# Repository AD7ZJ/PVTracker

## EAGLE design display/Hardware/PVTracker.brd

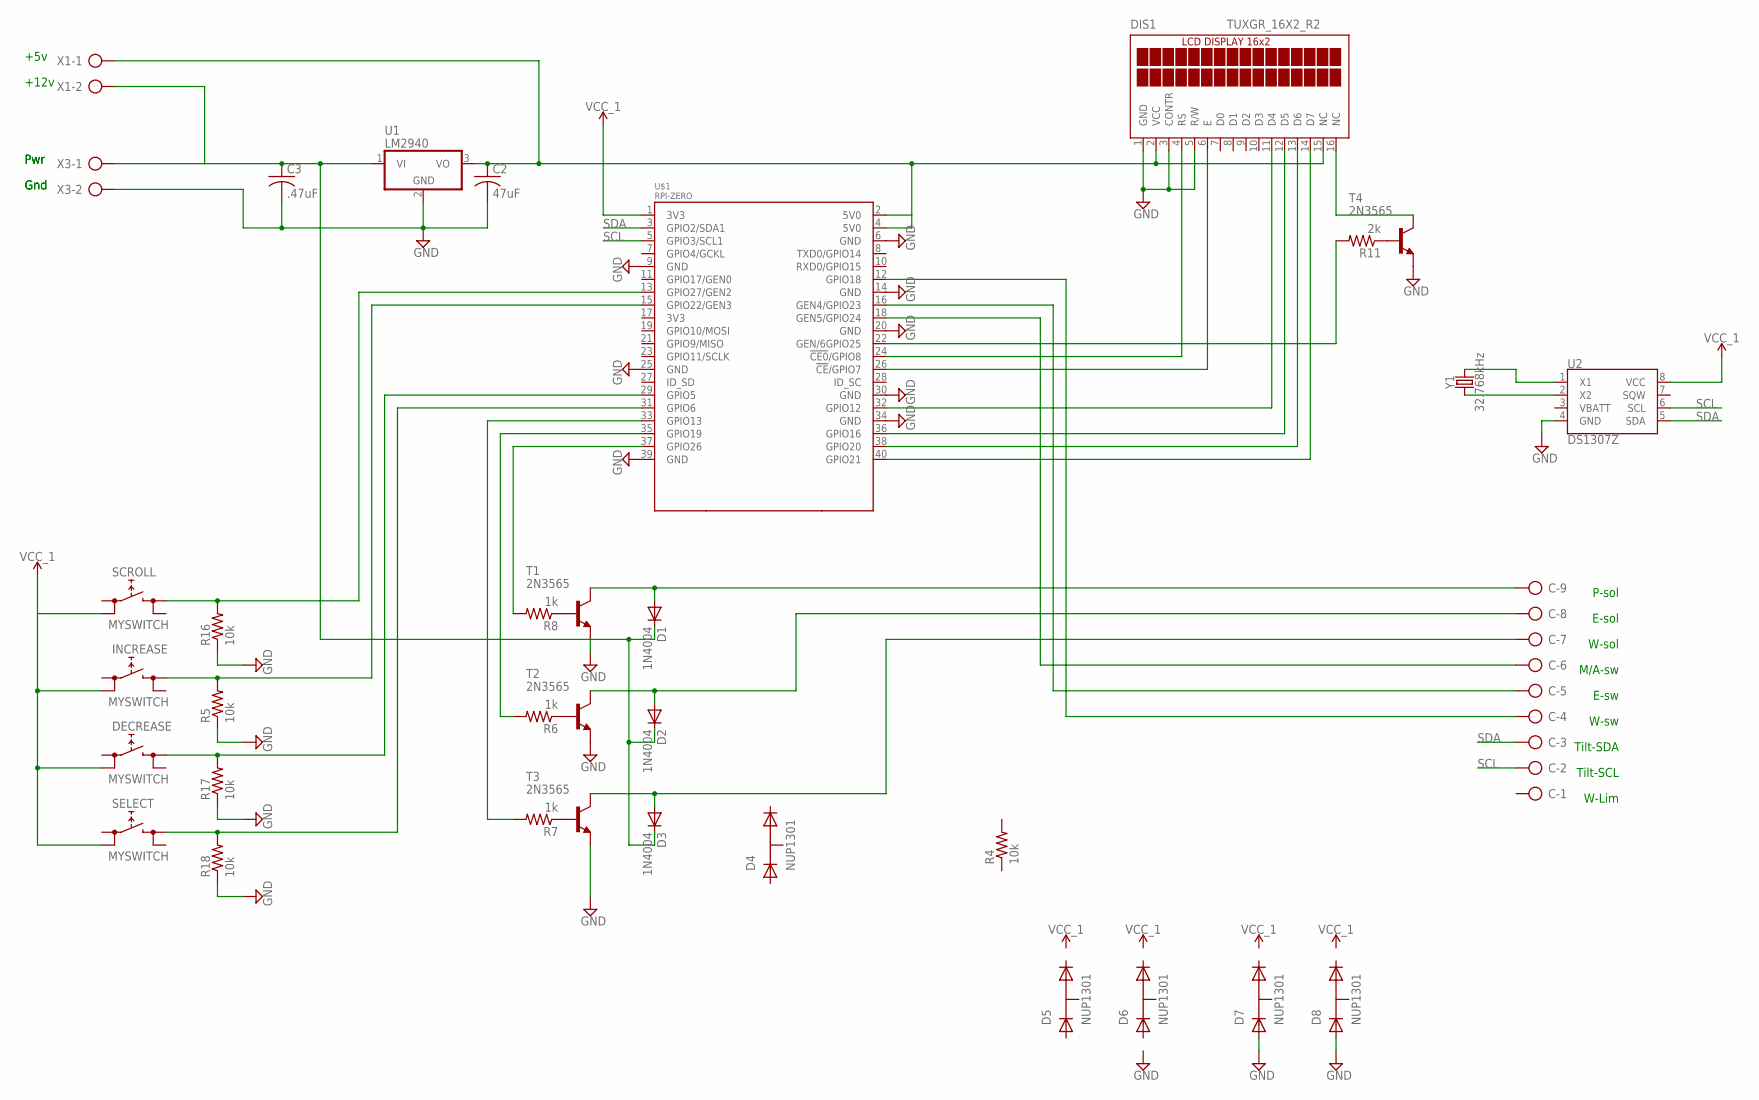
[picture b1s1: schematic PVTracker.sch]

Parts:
C: AK300/9
C2: 47uF; C025-030X050
C3: .47uF; C0805
D1, D2, D3: 1N4004; DO41-10
D4, D5, D6, D7, D8: NUP1301; SOT-23
DECREASE: MYSWITCH
DIS1: TUXGR_16X2_R2
INCREASE: MYSWITCH
R4, R5, R16, R17, R18: 10k; R0805
R6, R7, R8: 1k; R0805
R11: 2k; R0805
SCROLL: MYSWITCH
SELECT: MYSWITCH
T1, T2, T3, T4: 2N3565; TO92
U1: LM2940; SOT-223
U2: DS1307Z; SO08-0.15
U$1: RPI-ZERO; RASPBERRYPI_BASTELSTUBE_V13_RASPI_BOARD_B+_FULL
X1, X3: AK300/2
Y1: 32.768kHz; CRYSTAL-PTH-2X6-CYL

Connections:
3V3@1: U$1.1 (3V3)
5V0@1: C2.1, DIS1.2 (VCC), DIS1.15 (NC), U1.3 (VO), U$1.2 (5V0), U$1.4 (5V0), X1.1
GND: C2.2, C3.2, D7.1, D8.1, DIS1.1 (GND), DIS1.3 (CONTR), DIS1.5 (R/W), R5.1, R16.1, R17.1, R18.1, T1.3 (E), T2.3 (E), T3.3 (E), T4.3 (E), U1.2 (GND), U2.4 (GND), U$1.6 (GND), U$1.9 (GND), U$1.14 (GND), U$1.20 (GND), U$1.25 (GND), U$1.30 (GND), U$1.34 (GND), U$1.39 (GND), X3.2
unnamed: R11.2, U$1.22 (GEN/6GPIO25)
unnamed: C.5, U$1.16 (GEN4/GPIO23)
unnamed: DIS1.4 (RS), U$1.24 (!CE0!/GPIO8)
unnamed: DIS1.6 (E), U$1.26 (!CE!/GPIO7)
unnamed: DIS1.11 (D4), U$1.32 (GPIO12)
unnamed: DIS1.12 (D5), U$1.36 (GPIO16)
unnamed: DIS1.13 (D6), U$1.38 (GPIO20)
unnamed: DIS1.14 (D7), U$1.40 (GPIO21)
unnamed: R7.2, U$1.33 (GPIO13)
unnamed: R6.2, U$1.35 (GPIO19)
unnamed: R6.1, T2.2 (B)
unnamed: C.9, D1.A, T1.1 (C)
unnamed: C.8, D2.A, T2.1 (C)
unnamed: C.7, D3.A, T3.1 (C)
unnamed: C3.1, D1.C, D2.C, D3.C, U1.1 (VI), X1.2, X3.1
unnamed: R7.1, T3.2 (B)
unnamed: R8.2, U$1.37 (GPIO26)
unnamed: C.4, U$1.12 (GPIO18)
unnamed: U2.2 (X2), Y1.1
unnamed: R11.1, T4.2 (B)
unnamed: C.6, U$1.18 (GEN5/GPIO24)
unnamed: U2.1 (X1), Y1.2
unnamed: DIS1.16 (NC), T4.1 (C)
unnamed: R16.2, SCROLL.B0 (1), U$1.13 (GPIO27/GEN2)
unnamed: INCREASE.B0 (1), R5.2, U$1.15 (GPIO22/GEN3)
unnamed: DECREASE.B0 (1), R17.2, U$1.29 (GPIO5)
unnamed: R18.2, SELECT.B0 (1), U$1.31 (GPIO6)
unnamed: R8.1, T1.2 (B)
SCL: C.2, U2.6 (SCL), U$1.5 (GPIO3/SCL1)
SDA: C.3, U2.5 (SDA), U$1.3 (GPIO2/SDA1)
VCC_1: DECREASE.A0 (0), INCREASE.A0 (0), SCROLL.A0 (0), SELECT.A0 (0), U2.8 (VCC)

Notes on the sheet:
W-Lim
Tilt-SCL
Tilt-SDA
W-sw
E-sw
M/A-sw
W-sol
E-sol
P-sol
Pwr
Gnd
+12v
+5v

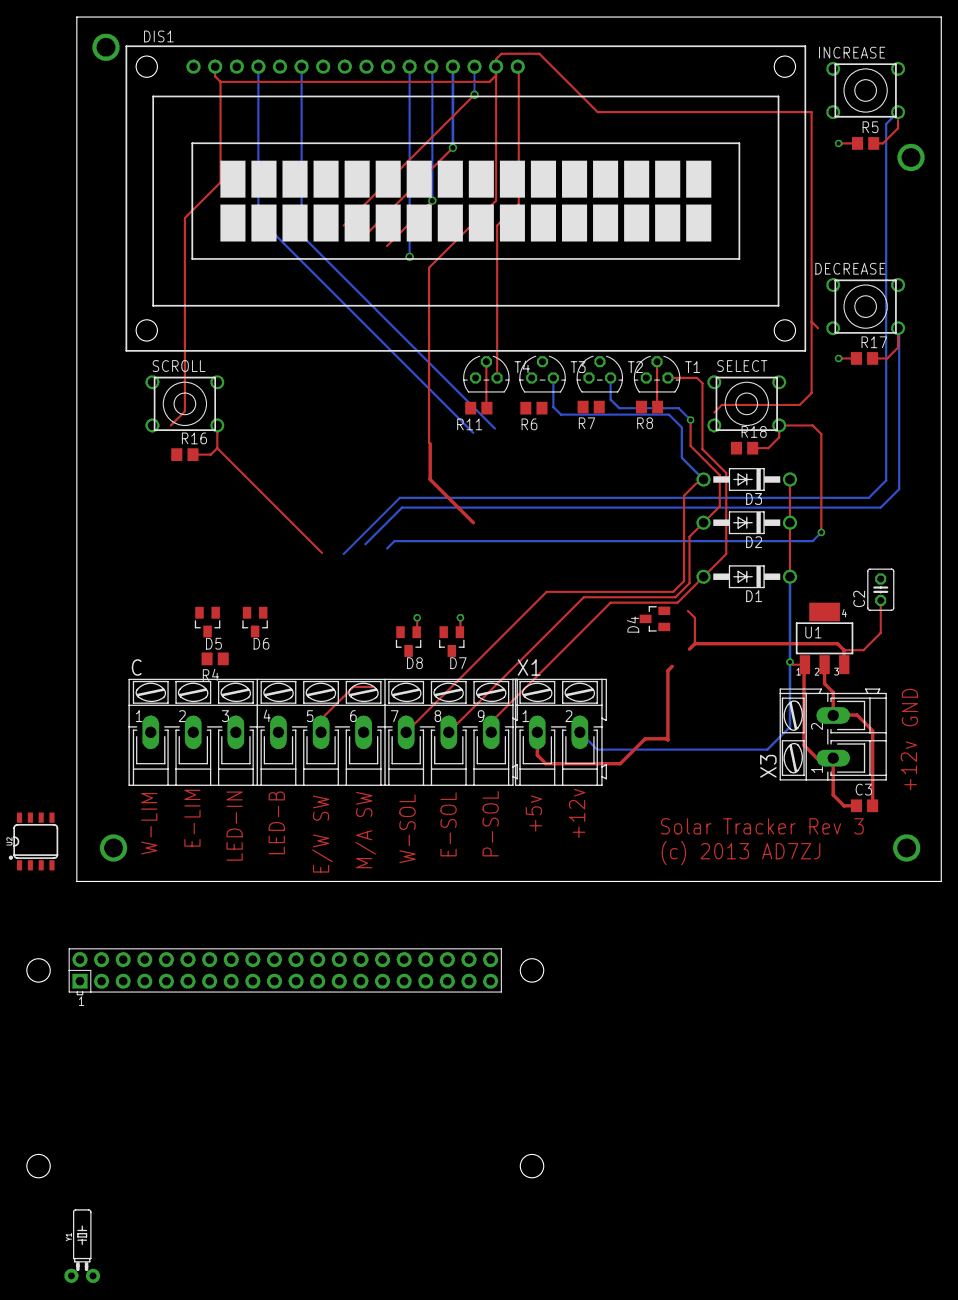
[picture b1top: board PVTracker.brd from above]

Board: 2 copper layers, 101.6 x 101.6 mm, 35 parts (0 on the bottom side), 33 nets.

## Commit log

2012-11-11 Initial commit of project
2012-11-12 Started adding GUI
2012-11-12 Filled out the GUI a bit more and added button handlers for increase/decrease
2012-11-12 Added EEPROM routines to save parameters persistently through a reset.
2012-11-12 Added a few more menus
2012-11-23 Added Eagle schematic and board layout to the project
2013-03-22 Initial commit of pic basic pro version of the tracking software
2013-03-22 Cleaned up the code a bit
2013-03-22 Switched to the PIC16F887
2013-03-22 Cleaned up the code a bit and simplified the tracking algorithm
2013-03-22 Added 'move safe' option to the menu and fixed initialization bug where parameters weren't read from EEPROM until going through the menu options.
2013-03-22 Increased safety delay so the 'move safe' routine won't time out when the array is moving very slowly (happens in really cold weather)
2013-03-22 Made the menu units more user-friendly (hh:mm:ss form) rather than 10ths of seconds and such
2014-01-11 Added pump time and backlight delay
2014-01-11 Added diode to LED input to keep it from swinging below the opamp supply rails
2020-11-06 start layout for raspberry pi based system
2020-12-28 Initial checkin of main.c for sensor
2020-12-28 Add serial driver
2020-12-28 Add initial ADXL345 driver, device ID read is working.
2020-12-28 Successfully reading data from all 3 axis
2020-12-28 Add self test to adxl driver.
2020-12-29 Send message 4 times per second Include status bit in message Enable optimizations
2020-12-29 Check in programming file
2020-12-29 General cleanup
2021-01-01 Initial commit of display stuff
2021-03-30 Save progress on sensor module
2021-11-15 Start of simulator
2021-11-15 start of menu structure
2021-11-15 Send up/down events for increase/decrease buttons
2021-11-16 Added a couple menus
2021-11-17 Handle repeat on button held
2021-11-20 add more menus, add man/auto, east west buttons.
